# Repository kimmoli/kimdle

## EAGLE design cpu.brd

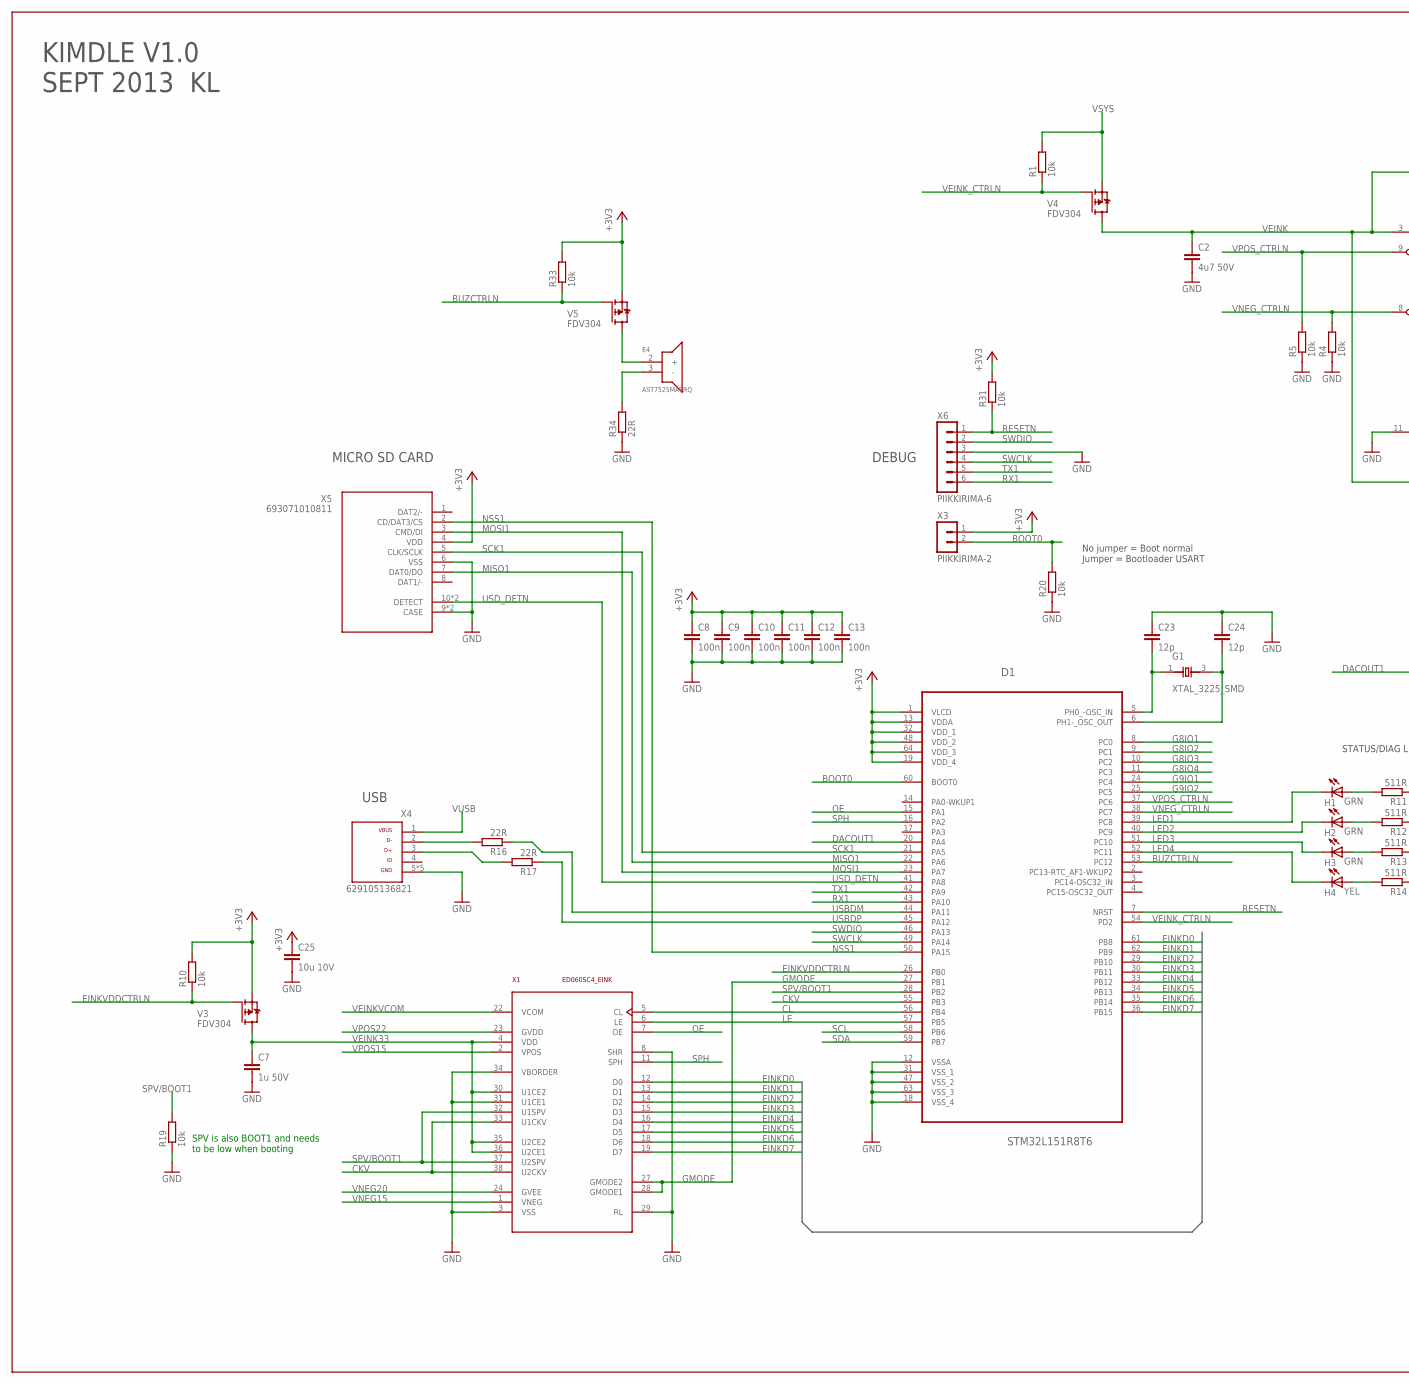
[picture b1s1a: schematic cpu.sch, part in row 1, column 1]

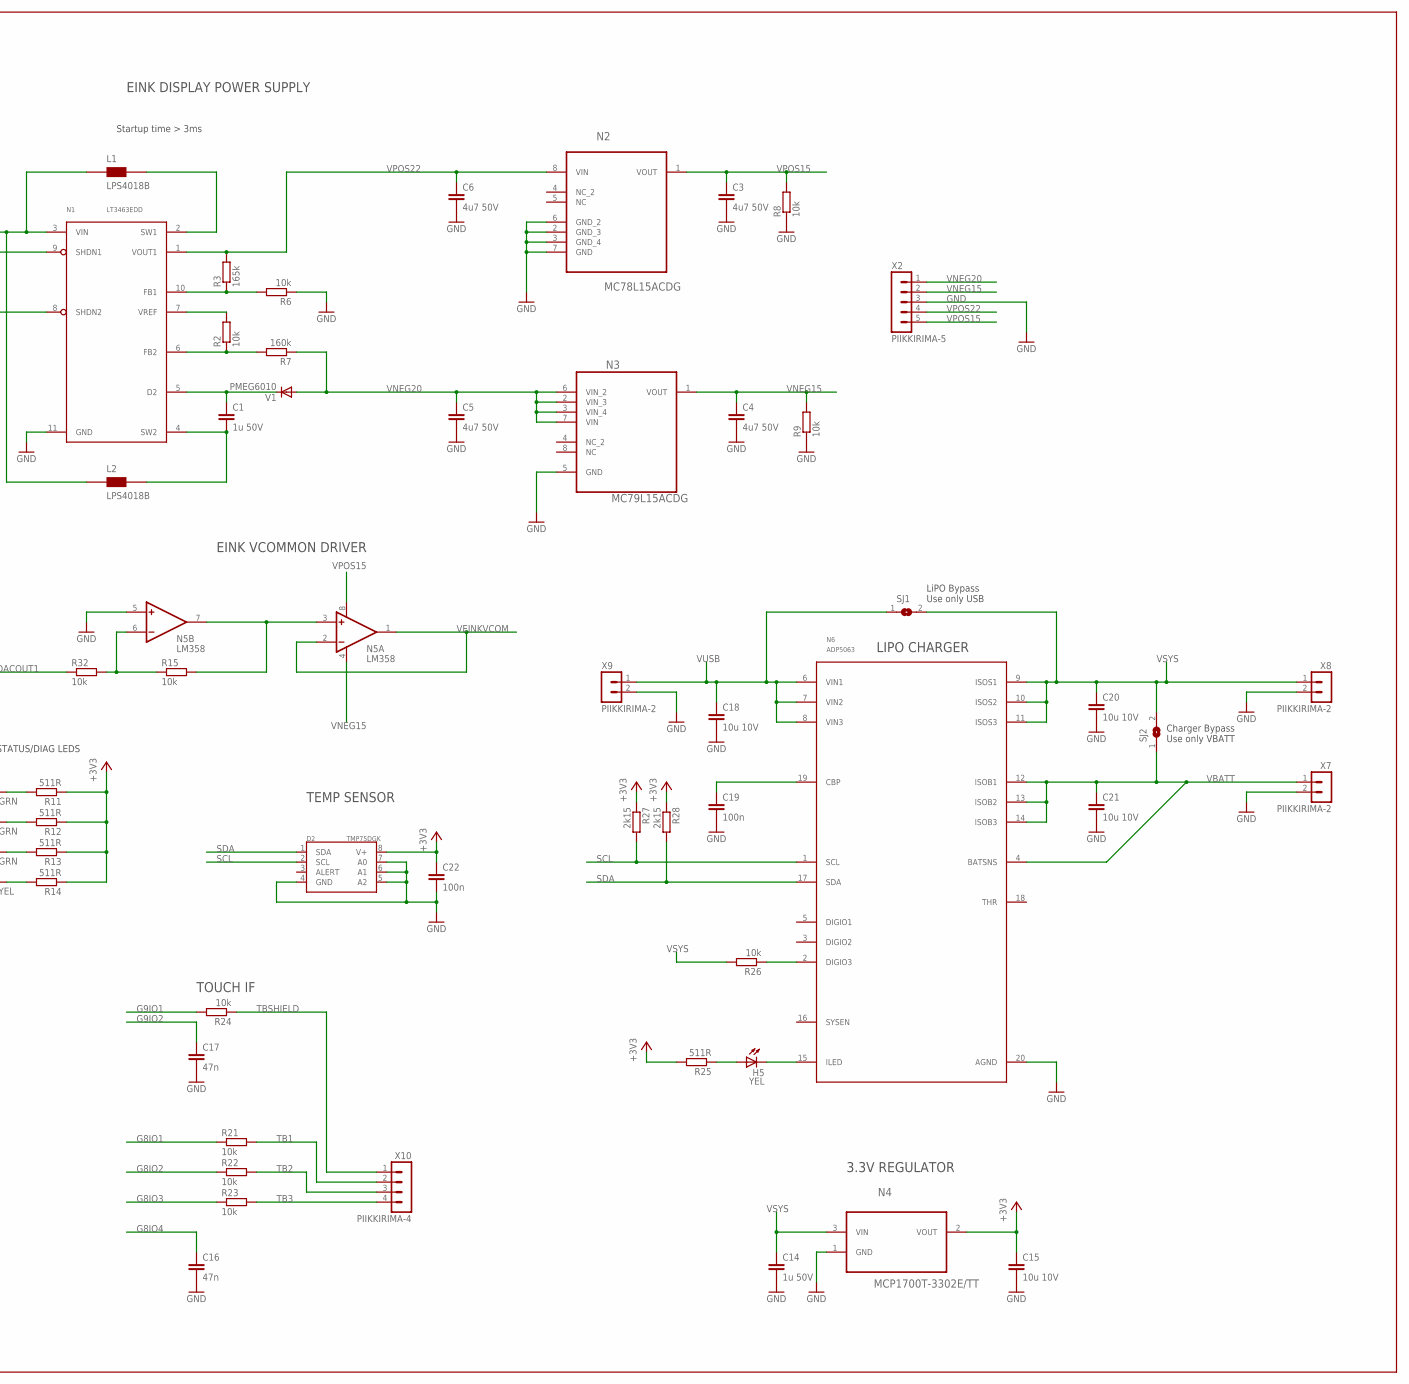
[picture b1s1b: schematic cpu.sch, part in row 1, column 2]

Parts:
C1, C7, C14: 1u 50V; C0805
C2, C3, C4, C5, C6: 4u7 50V; C0805
C8, C9, C10, C11, C12, C13, C19, C22: 100n; C0603
C15, C18, C20, C21, C25: 10u 10V; C0805
C16, C17: 47n; C0805
C23, C24: 12p; C0603
D1: STM32L151R8T6; QFP50P1200X1200X160-64N
D2: TMP75DGK; MSOP8
E4: AST7525MATRQ
G1: XTAL_3225_SMD; X_3225
H1, H2, H3: GRN; CHIP-LED0603
H4, H5: YEL; CHIP-LED0603
L1, L2: LPS4018B; LPS4018_V2
N1: LT3463EDD; DFN300X300X80-11N
N2: MC78L15ACDG; SOIC127P600X175-8N
N3: MC79L15ACDG; SOIC127P600X175-8N
N4: MCP1700T-3302E/TT; SOT95P237X112-3N
N5: LM358; SOP65P490X110-8N
N6: ADP5063; QFN50P400X400X80-21N
R1, R2, R4, R5, R6, R8, R9, R10, R15, R19, R20, R21, R22, R23, R24, R26, R31, R32, R33: 10k; R0603
R3: 165k; R0603
R7: 160k; R0603
R11, R12, R13, R14, R25: 511R; R0603
R16, R17, R34: 22R; R0603
R27, R28: 2k15; R0603
SJ1, SJ2: SJ; SJ-SMALL
V1: PMEG6010; SOD323-R
V3, V4, V5: FDV304; SOT23
X1: ED060SC4_EINK; FH26-39S-0.3SHW
X2: PIIKKIRIMA-5
X3, X7, X8, X9: PIIKKIRIMA-2
X4: 629105136821
X5: 693071010811
X6: PIIKKIRIMA-6
X10: PIIKKIRIMA-4

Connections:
+3V3: C8.1, C9.1, C10.1, C11.1, C12.1, C13.1, C15.1, C22.1, C25.1, D1.1 (VLCD), D1.13 (VDDA), D1.19 (VDD_4), D1.32 (VDD_1), D1.48 (VDD_2), D1.64 (VDD_3), D2.8 (V+), N4.2 (VOUT), R10.2, R11.1, R12.1, R13.1, R14.1, R25.2, R27.1, R28.1, R31.2, R33.2, V3.2 (S), V5.2 (S), X3.1, X5.4 (VDD)
BOOT0: D1.60 (BOOT0), R20.2, X3.2
BUZCTRLN: D1.53 (PC12), R33.1, V5.1 (G)
CKV: D1.55 (PB3), X1.33 (U1CKV), X1.38 (U2CKV)
CL: D1.56 (PB4), X1.5 (CL)
DACOUT1: D1.20 (PA4), R32.1
EINKD0: D1.61 (PB8), X1.12 (D0)
EINKD1: D1.62 (PB9), X1.13 (D1)
EINKD2: D1.29 (PB10), X1.14 (D2)
EINKD3: D1.30 (PB11), X1.15 (D3)
EINKD4: D1.33 (PB12), X1.16 (D4)
EINKD5: D1.34 (PB13), X1.17 (D5)
EINKD6: D1.35 (PB14), X1.18 (D6)
EINKD7: D1.36 (PB15), X1.19 (D7)
EINKVDDCTRLN: D1.26 (PB0), R10.1, V3.1 (G)
G8IO1: D1.8 (PC0), R21.1
G8IO2: D1.9 (PC1), R22.1
G8IO3: D1.10 (PC2), R23.1
G8IO4: C16.1, D1.11 (PC3)
G9IO1: D1.24 (PC4), R24.2
G9IO2: C17.1, D1.25 (PC5)
GMODE: D1.27 (PB1), X1.27 (GMODE2), X1.28 (GMODE1)
GND: C2.2, C3.2, C4.2, C5.2, C6.2, C7.2, C8.2, C9.2, C10.2, C11.2, C12.2, C13.2, C14.2, C15.2, C16.2, C17.2, C18.2, C19.2, C20.2, C21.2, C22.2, C23.1, C24.1, C25.2, D1.12 (VSSA), D1.18 (VSS_4), D1.31 (VSS_1), D1.47 (VSS_2), D1.63 (VSS_3), D2.4 (GND), D2.5 (A2), D2.6 (A1), D2.7 (A0), N1.11 (GND), N2.2 (GND_3), N2.3 (GND_4), N2.6 (GND_2), N2.7 (GND), N3.5 (GND), N4.1 (GND), N5.5 (+IN), N6.20 (AGND), R4.1, R5.1, R6.1, R8.1, R9.1, R19.1, R20.1, R34.1, X1.3 (VSS), X1.8 (SHR), X1.29 (RL), X1.31 (U1CE1), X1.34 (VBORDER), X2.3, X4.5, X4.Z1 (5), X4.Z2 (5), X4.Z3 (5), X4.Z4 (5), X5.6 (VSS), X5.9 (CASE), X5.9B (CASE), X6.3, X7.2, X8.2, X9.2
LE: D1.57 (PB5), X1.6 (LE)
LED1: D1.39 (PC8), H1.C
LED2: D1.40 (PC9), H2.C
LED3: D1.51 (PC10), H3.C
LED4: D1.52 (PC11), H4.C
MISO1: D1.22 (PA6), X5.7 (DAT0/DO)
MOSI1: D1.23 (PA7), X5.3 (CMD/DI)
unnamed: C1.1, N1.5 (D2), V1.C
unnamed: R17.2, X4.3
unnamed: N1.6 (FB2), R2.1, R7.2
unnamed: R16.2, X4.2
unnamed: E4.3 (-), R34.2
unnamed: L1.2 (B), N1.2 (SW1)
unnamed: C1.2, L2.2 (B), N1.4 (SW2)
unnamed: N5.3 (+IN), N5.7 (OUT), R15.2
unnamed: N1.7 (VREF), R2.2
unnamed: H1.A, R11.2
unnamed: N1.10 (FB1), R3.1, R6.2
unnamed: C23.2, D1.5 (PH0_-OSC_IN), G1.1 (X1)
unnamed: H2.A, R12.2
unnamed: C24.2, D1.6 (PH1-_OSC_OUT), G1.3 (X2)
unnamed: H3.A, R13.2
unnamed: H4.A, R14.2
unnamed: N5.6 (-IN), R15.1, R32.2
unnamed: H5.C, N6.15 (ILED)
unnamed: C19.1, N6.19 (CBP)
unnamed: H5.A, R25.1
unnamed: N6.2 (DIGIO3), R26.1
NSS1: D1.50 (PA15), X5.2 (CD/DAT3/CS)
OE: D1.15 (PA1), X1.7 (OE)
RESETN: D1.7 (NRST), R31.1, X6.1
RX1: D1.43 (PA10), X6.6
SCK1: D1.21 (PA5), X5.5 (CLK/SCLK)
SCL: D1.58 (PB6), D2.2 (SCL), N6.1 (SCL), R27.2
SDA: D1.59 (PB7), D2.1 (SDA), N6.17 (SDA), R28.2
SPH: D1.16 (PA2), X1.11 (SPH)
SPV/BOOT1: D1.28 (PB2), R19.2, X1.32 (U1SPV), X1.37 (U2SPV)
SWCLK: D1.49 (PA14), X6.4
SWDIO: D1.46 (PA13), X6.2
TB1: R21.2, X10.2
TB2: R22.2, X10.3
TB3: R23.2, X10.4
TBSHIELD: R24.1, X10.1
TX1: D1.42 (PA9), X6.5
USBDM: D1.44 (PA11), R16.1
USBDP: D1.45 (PA12), R17.1
USD_DETN: D1.41 (PA8), X5.10 (DETECT), X5.10B (DETECT)
VBATT: C21.1, N6.4 (BATSNS), N6.12 (ISOB1), N6.13 (ISOB2), N6.14 (ISOB3), SJ2.1, X7.1
VEINK: C2.1, L1.1 (A), L2.1 (A), N1.3 (VIN), V4.3 (D)
VEINK1: E4.2 (+), V5.3 (D)
VEINK33: C7.1, V3.3 (D), X1.4 (VDD), X1.30 (U1CE2), X1.35 (U2CE2), X1.36 (U2CE1)
VEINKVCOM: N5.1 (OUT), N5.2 (-IN), X1.22 (VCOM)
VEINK_CTRLN: D1.54 (PD2), R1.1, V4.1 (G)
VNEG15: C4.1, N3.1 (VOUT), N5.4 (V-), R9.2, X1.1 (VNEG), X2.2
VNEG20: C5.1, N3.2 (VIN_3), N3.3 (VIN_4), N3.6 (VIN_2), N3.7 (VIN), R7.1, V1.A, X1.24 (GVEE), X2.1
VNEG_CTRLN: D1.38 (PC7), N1.8 (SHDN2), R4.2
VPOS15: C3.1, N2.1 (VOUT), N5.8 (V+), R8.2, X1.2 (VPOS), X2.5
VPOS22: C6.1, N1.1 (VOUT1), N2.8 (VIN), R3.2, X1.23 (GVDD), X2.4
VPOS_CTRLN: D1.37 (PC6), N1.9 (SHDN1), R5.2
VSYS: C14.1, C20.1, N4.3 (VIN), N6.9 (ISOS1), N6.10 (ISOS2), N6.11 (ISOS3), R1.2, R26.2, SJ1.2, SJ2.2, V4.2 (S), X8.1
VUSB: C18.1, N6.6 (VIN1), N6.7 (VIN2), N6.8 (VIN3), SJ1.1, X4.1, X9.1

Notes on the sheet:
STATUS/DIAG LEDS
DEBUG
USB
MICRO SD CARD
SPV is also BOOT1 and needs to be low when booting
No jumper = Boot normal Jumper = Bootloader USART
TOUCH IF
LIPO CHARGER
3.3V REGULATOR
EINK DISPLAY POWER SUPPLY
LiPO Bypass Use only USB
Charger Bypass Use only VBATT
KIMDLE V1.0 SEPT 2013 KL
EINK VCOMMON DRIVER
Startup time > 3ms
TEMP SENSOR

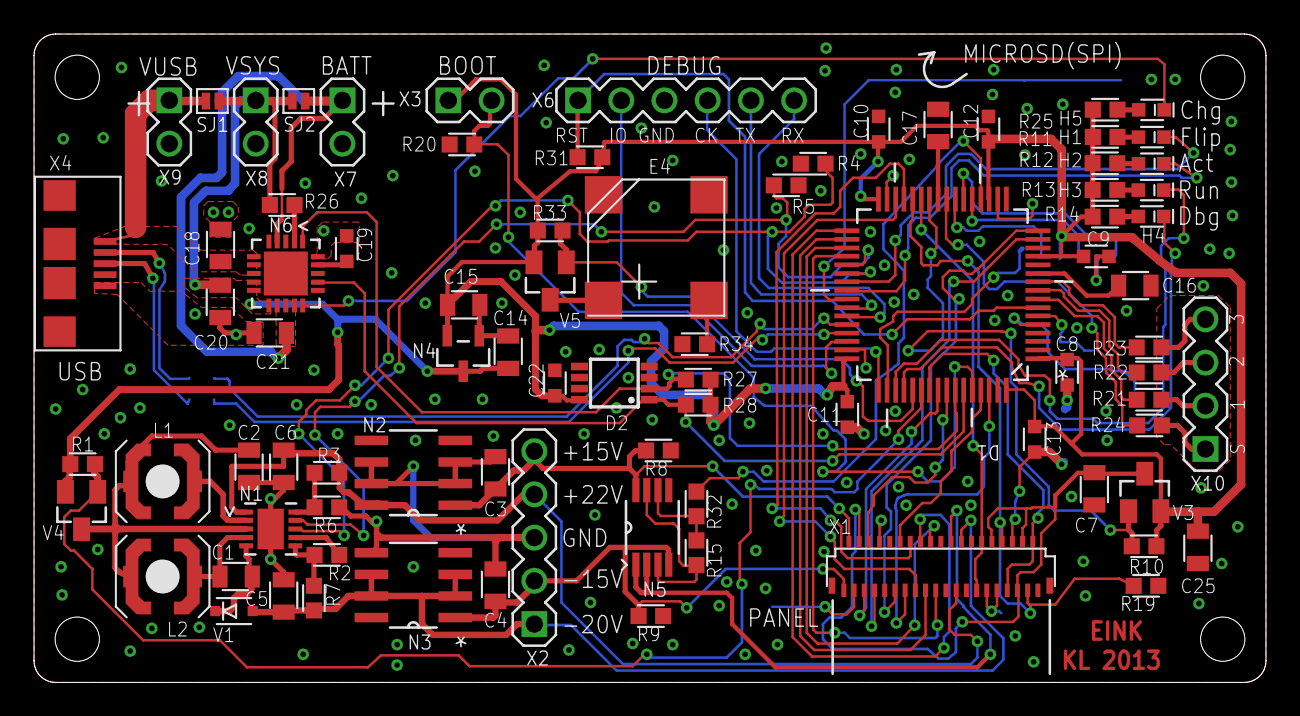
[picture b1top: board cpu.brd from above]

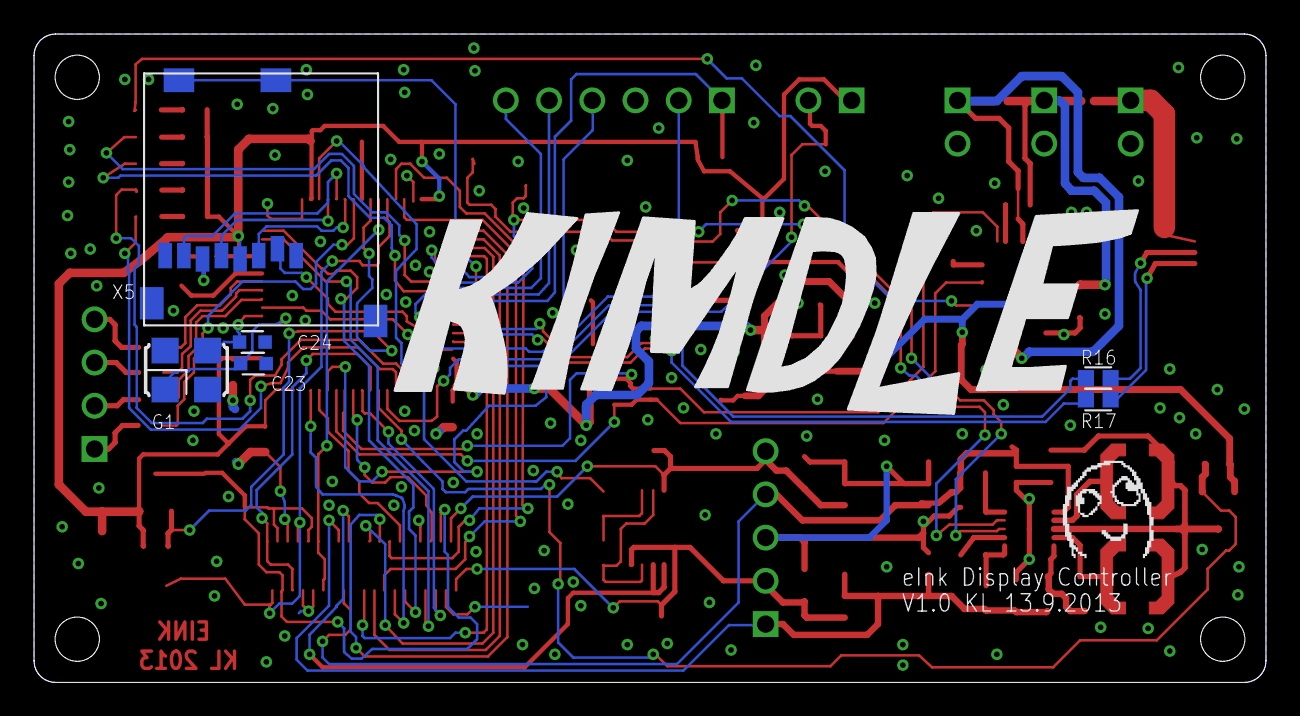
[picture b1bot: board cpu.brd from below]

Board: 2 copper layers, 72.4 x 38.1 mm, 90 parts (7 on the bottom side), 84 nets.

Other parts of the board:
U$3: DAFUG

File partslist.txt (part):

Partlist

Exported from cpu.sch at 13.9.2013 15:01:23

EAGLE Version 6.4.0 Copyright (c) 1988-2013 CadSoft

Assembly variant: 

Part     Value             Device            Package                 Library                                 Sheet

C1       1u 50V            C-EUC0805         C0805                   rcl                                     1
C2       4u7 50V           C-EUC0805         C0805                   rcl                                     1
C3       4u7 50V           C-EUC0805         C0805                   rcl                                     1
C4       4u7 50V           C-EUC0805         C0805                   rcl                                     1
C5       4u7 50V           C-EUC0805         C0805                   rcl                                     1
C6       4u7 50V           C-EUC0805         C0805                   rcl                                     1
C7       1u 50V            C-EUC0805         C0805                   rcl                                     1
C8       100n              C-EUC0603         C0603                   rcl                                     1
C9       100n              C-EUC0603         C0603                   rcl                                     1
C10      100n              C-EUC0603         C0603                   rcl                                     1
C11      100n              C-EUC0603         C0603                   rcl                                     1
C12      100n              C-EUC0603         C0603                   rcl                                     1
C13      100n              C-EUC0603         C0603                   rcl                                     1
C14      1u 50V            C-EUC0805         C0805                   rcl                                     1
C15      10u 10V           C-EUC0805         C0805                   rcl                                     1
C16      47n               C-EUC0805         C0805                   rcl                                     1
C17      47n               C-EUC0805         C0805                   rcl                                     1
C18      10u 10V           C-EUC0805         C0805                   rcl                                     1
C19      100n              C-EUC0603         C0603                   rcl                                     1
C20      10u 10V           C-EUC0805         C0805                   rcl                                     1
C21      10u 10V           C-EUC0805         C0805                   rcl                                     1
C22      100n              C-EUC0603         C0603                   rcl                                     1
C23      12p               C-EUC0603         C0603                   rcl                                     1
C24      12p               C-EUC0603         C0603                   rcl                                     1
C25      10u 10V           C-EUC0805         C0805                   rcl                                     1
D1       STM32L151R8T6     STM32L151R8T6     QFP50P1200X1200X160-64N ST Microelctronics_By_element14_Batch_1 1
D2       TMP75DGK          TMP75DGK          MSOP8                   ti_tmp                                  1
E4       AST7525MATRQ      AST7525MATRQ      AST7525MATRQ            OMAT_IC                                 1
G1       XTAL_3225_SMD     XTAL_3225_SMD     X_3225                  OMAT_IC                                 1
H1       GRN               LEDCHIP-LED0603   CHIP-LED0603            OMAT_IC                                 1
H2       GRN               LEDCHIP-LED0603   CHIP-LED0603            OMAT_IC                                 1
H3       GRN               LEDCHIP-LED0603   CHIP-LED0603            OMAT_IC                                 1
H4       YEL               LEDCHIP-LED0603   CHIP-LED0603            OMAT_IC                                 1
H5       YEL               LEDCHIP-LED0603   CHIP-LED0603            OMAT_IC                                 1
L1       LPS4018B          LPS4018B          LPS4018_V2              OMAT_IC                                 1
L2       LPS4018B          LPS4018B          LPS4018_V2              OMAT_IC                                 1
N1       LT3463EDD         LT3463EDD         DFN300X300X80-11N       OMAT_IC                                 1
N2       MC78L15ACDG       MC78L15ACDG       SOIC127P600X175-8N      ON Semiconductor_By_element14_Batch_1   1
N3       MC79L15ACDG       MC79L15ACDG       SOIC127P600X175-8N      ON Semiconductor_By_element14_Batch_1   1
N4       MCP1700T-3302E/TT MCP1700T-3302E/TT SOT95P237X112-3N        Microchip_By_element14_Batch_1          1
N5       LM358             MAX412CPAMSOP     SOP65P490X110-8N        OMAT_IC                                 1
N6       ADP5063           ADP5063           QFN50P400X400X80-21N    OMAT_IC                                 1
R1       10k               R-EU_R0603        R0603                   rcl                                     1
R2       10k               R-EU_R0603        R0603                   rcl                                     1
R3       165k              R-EU_R0603        R0603                   rcl                                     1
R4       10k               R-EU_R0603        R0603                   rcl                                     1
R5       10k               R-EU_R0603        R0603                   rcl                                     1
R6       10k               R-EU_R0603        R0603                   rcl                                     1
R7       160k              R-EU_R0603        R0603                   rcl                                     1
R8       10k               R-EU_R0603        R0603                   rcl                                     1
R9       10k               R-EU_R0603        R0603                   rcl                                     1
R10      10k               R-EU_R0603        R0603                   rcl                                     1
R11      511R              R-EU_R0603        R0603                   rcl                                     1
R12      511R              R-EU_R0603        R0603                   rcl                                     1
R13      511R              R-EU_R0603        R0603                   rcl                                     1
R14      511R              R-EU_R0603        R0603                   rcl                                     1
R15      10k               R-EU_R0603        R0603                   rcl                                     1
R16      22R               R-EU_R0603        R0603                   rcl                                     1
R17      22R               R-EU_R0603        R0603                   rcl                                     1
R19      10k               R-EU_R0603        R0603                   rcl                                     1
R20      10k               R-EU_R0603        R0603                   rcl                                     1
R21      10k               R-EU_R0603        R0603                   rcl                                     1
R22      10k               R-EU_R0603        R0603                   rcl                                     1
R23      10k               R-EU_R0603        R0603                   rcl                                     1
R24      10k               R-EU_R0603        R0603                   rcl                                     1
R25      511R              R-EU_R0603        R0603                   rcl                                     1
R26      10k               R-EU_R0603        R0603                   rcl                                     1
R27      2k15              R-EU_R0603        R0603                   rcl                                     1
R28      2k15              R-EU_R0603        R0603                   rcl                                     1
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
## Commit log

2013-09-10 First commit
    EINK Powersupply
2013-09-11 Schematic should be complete
    Schematic should have all parts now
2013-09-11 Buzzer added
    Added smalles affordable buzzer.
2013-09-11 Layout commit 1
    First commit with some layout/placement
2013-09-11 All parts first time onboard - placed
    Touchbuttons also prelocated for OSHpark testing
2013-09-11 Layout cont
    Flex connector first routing attempt. not nice. too many vias...
2013-09-12 Layout cont2
    17 airwires left.
    touch buttons removed from cpu board
2013-09-12 Layout complete
    First completed layout , Airwires 0
2013-09-12 Finetuning
    USB connector moved closer to edge etc.
2013-09-12 HSE Crystal added
    Added G1, 3.2x2.5 mm crystal. bottom.
2013-09-12 Bypass, tuning
    One 0805 bulk bypass added.
    GND fills fixed close G1
2013-09-12 Power control signals added
    DCDC Converter enables (all three) were missing from schematic.
    Processor grounds connected too.
2013-09-13 Final - ready to order
    Part values added
2013-09-13 KIMDLE logo
    Logo added - saying KIMDLE on bottom
2013-09-13 KIMDLE logo revisited
    The imported bitmap was rejected by OSHpark. made my own from polygons
2016-11-20 schema and gerber pdf
